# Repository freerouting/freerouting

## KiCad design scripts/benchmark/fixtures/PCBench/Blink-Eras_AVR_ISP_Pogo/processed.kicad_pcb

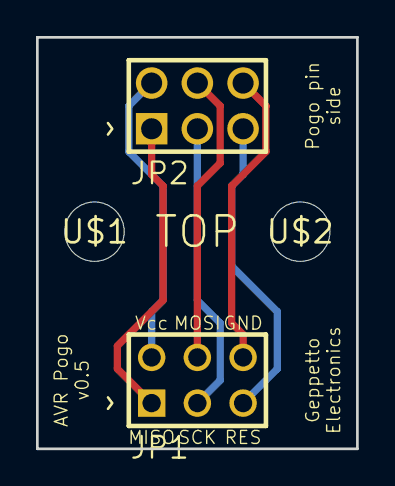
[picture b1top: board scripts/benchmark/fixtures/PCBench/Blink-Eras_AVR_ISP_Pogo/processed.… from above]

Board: 2 copper layers, 17.8 x 22.9 mm, 4 parts (0 on the bottom side), 6 nets.

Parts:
JP1: AVR-ISP-6VERT; AVR-ISP-6
JP2: POGO-PIN-ISP46MIL; AVR-PPINS-46-6ISP
U$1, U$2: STAND-OFF

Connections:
unnamed: JP1.2, JP2.2
unnamed: JP1.4, JP2.4
unnamed: JP1.6, JP2.6
unnamed: JP1.1, JP2.1
unnamed: JP1.3, JP2.3
unnamed: JP1.5, JP2.5

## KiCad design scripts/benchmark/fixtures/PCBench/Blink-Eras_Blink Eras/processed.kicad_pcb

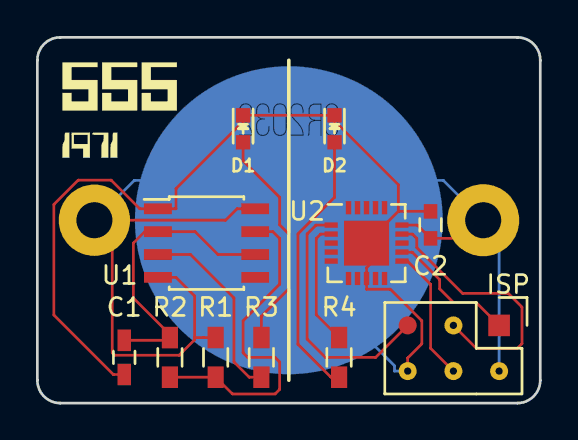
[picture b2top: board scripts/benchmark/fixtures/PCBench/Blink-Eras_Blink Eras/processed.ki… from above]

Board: 2 copper layers, 27.9 x 20.3 mm, 12 parts (1 on the bottom side), 12 nets.

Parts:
BT1: CR2032; Big_Pad_Battery
C1: 1µ; C_0603_HandSoldering
C2: 1µ; C_0603
D1: Red; LED_0603
D2: Green; LED_0603
P1: ISP; ISP_Pogo_5-thru
R1: 1K; R_0603_HandSoldering
R2: 470K; R_0603_HandSoldering
R3: 68; R_0603_HandSoldering
R4: 56; R_0603_HandSoldering
U1: ICM7555; SOIC-8_3.9x4.9mm_Pitch1.27mm
U2: ATTINY85-M; QFN-20-1EP_4x4mm_Pitch0.5mm

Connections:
/MISO: P1.1, U2.12
/MOSI: P1.4, U2.11
/SCK: P1.3, U2.14
/~RESET~: P1.5, U2.1
GND: BT1.2, C1.2, C2.2, D1.1, D2.1, P1.6, U1.1, U2.8
unnamed: C1.1, R2.2, U1.2, U1.6
unnamed: D1.2, R3.2
unnamed: D2.2, R4.2
unnamed: R1.2, R2.1, U1.7
unnamed: R3.1, U1.3
unnamed: R4.1, U2.2
VCC: BT1.1, C2.1, P1.2, R1.1, U1.4, U1.8, U2.15

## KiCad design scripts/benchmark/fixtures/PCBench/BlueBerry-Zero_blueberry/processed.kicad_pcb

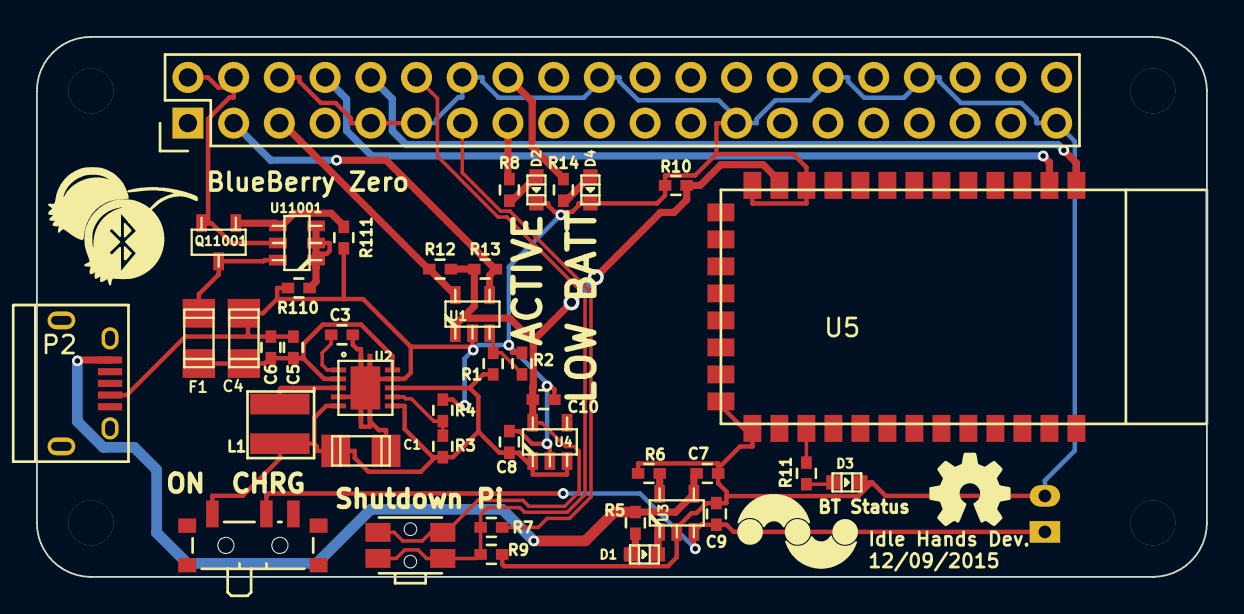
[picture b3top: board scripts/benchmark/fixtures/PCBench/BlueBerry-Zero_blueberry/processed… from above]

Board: 2 copper layers, 65.0 x 30.0 mm, 43 parts (1 on the bottom side), 29 nets.

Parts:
C1, C4: 10uF; c_1206
C3, C6: 0.1uF; C_0402_Hand
C5: 1uF; C_0402_Hand
C7, C9: 4.7uF; C_0402_Hand
C8, C10: 1.0uf; C_0402_Hand
D1, D2, D3, D4: Led_Small; Led_0603
F1: FUSE; c_1206
L1: 2.2uH; I_1212
P1: Raspberry_Pi_+_Conn; Pin_Header_Straight_2x20
P2: USB_B; USB_Micro-B
P3: CONN_01X02; Connectors_JST_S2B-PH-K
Q11001: BSS138; SOT23
R1: 470K; R_0402_Hand
R2: 1.7M; R_0402_Hand
R3: 3.4M; R_0402_Hand
R4: 250k; R_0402_Hand
R5, R7, R8, R11, R14: 1K; R_0402_Hand
R6: 2K; R_0402_Hand
R9, R10: 10K; R_0402_Hand
R12, R13: 22K; R_0402_Hand
R110: 10k; R_0402_Hand
R111: 47k; R_0402_Hand
SW1: Switch_SPDT_x2; SW_SPDT_PCM12
SW2: SW_PUSH; SW_SPST_EVQP7C
U1: MCP3021; sot23-5
U2: TPS61202; PVSON-10
U3: MCP73831; sot23-5
U4: TLV71333DBV; sot23-5
U5: HC-06
U11001: DMMT5401; sot23-6

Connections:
+3V3: C10.1, R10.2, R12.1, R13.1, SW2.1, U1.1, U4.5, U5.12
+5V: F1.2, Q11001.3, U11001.6
/BATT: C9.1, P3.1, SW1.2, U3.3
/BATT5V: C4.1, C5.1, C6.1, F1.1, U2.2, U2.10
/LOW_BATT_LED: P1.16, R14.2
/PI_I2C_SCL: P1.5, R12.2, U1.5
/PI_I2C_SDA: P1.3, R13.2, U1.4
/PI_UART_RXD: P1.10, U5.1
/PI_UART_TXD: P1.8, U5.2
/SAFESHUT_LED: P1.15, R8.2
/SHUTDOWN: P1.13, R7.1
/USB5V: C7.1, P2.1, R5.2, U3.4
/UVLO: R3.2, R4.1, U2.7
/UVSHUTDOWN: P1.12, R7.2, R9.1, SW2.2
/VBATT: C1.1, C8.1, L1.1, R1.1, R3.1, SW1.1, U2.5, U2.6, U2.8, U4.1, U4.3
/sheet56654A17/5V_MCU: P1.2, P1.4, Q11001.2, U11001.5
GND: C1.2, C3.2, C4.2, C5.2, C6.2, C7.2, C8.2, C9.2, C10.2, D2.1, D3.1, D4.1, P1.6, P1.9, P1.11, P1.14, P1.20, P1.25, P1.30, P1.34, P1.39, P2.4, P3.2, R2.2, R4.2, R6.2, R9.2, R10.1, R110.2, R111.2, U1.2, U2.4, U2.9, U3.2, U4.2, U5.11, U5.13, U5.21, U5.22
unnamed: C3.1, U2.1
unnamed: D1.1, U3.1
unnamed: D1.2, R5.1
unnamed: D2.2, R8.1
unnamed: D3.2, R11.1
unnamed: D4.2, R14.1
unnamed: L1.2, U2.3
unnamed: Q11001.1, R111.1, U11001.4
unnamed: R1.2, R2.1, U1.3
unnamed: R6.1, U3.5
unnamed: R11.2, U5.24
unnamed: R110.1, U11001.1, U11001.2, U11001.3
